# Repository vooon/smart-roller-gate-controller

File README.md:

# smart-roller-gate-controller
ESP32 based roller gate controller with ZigBee remotes

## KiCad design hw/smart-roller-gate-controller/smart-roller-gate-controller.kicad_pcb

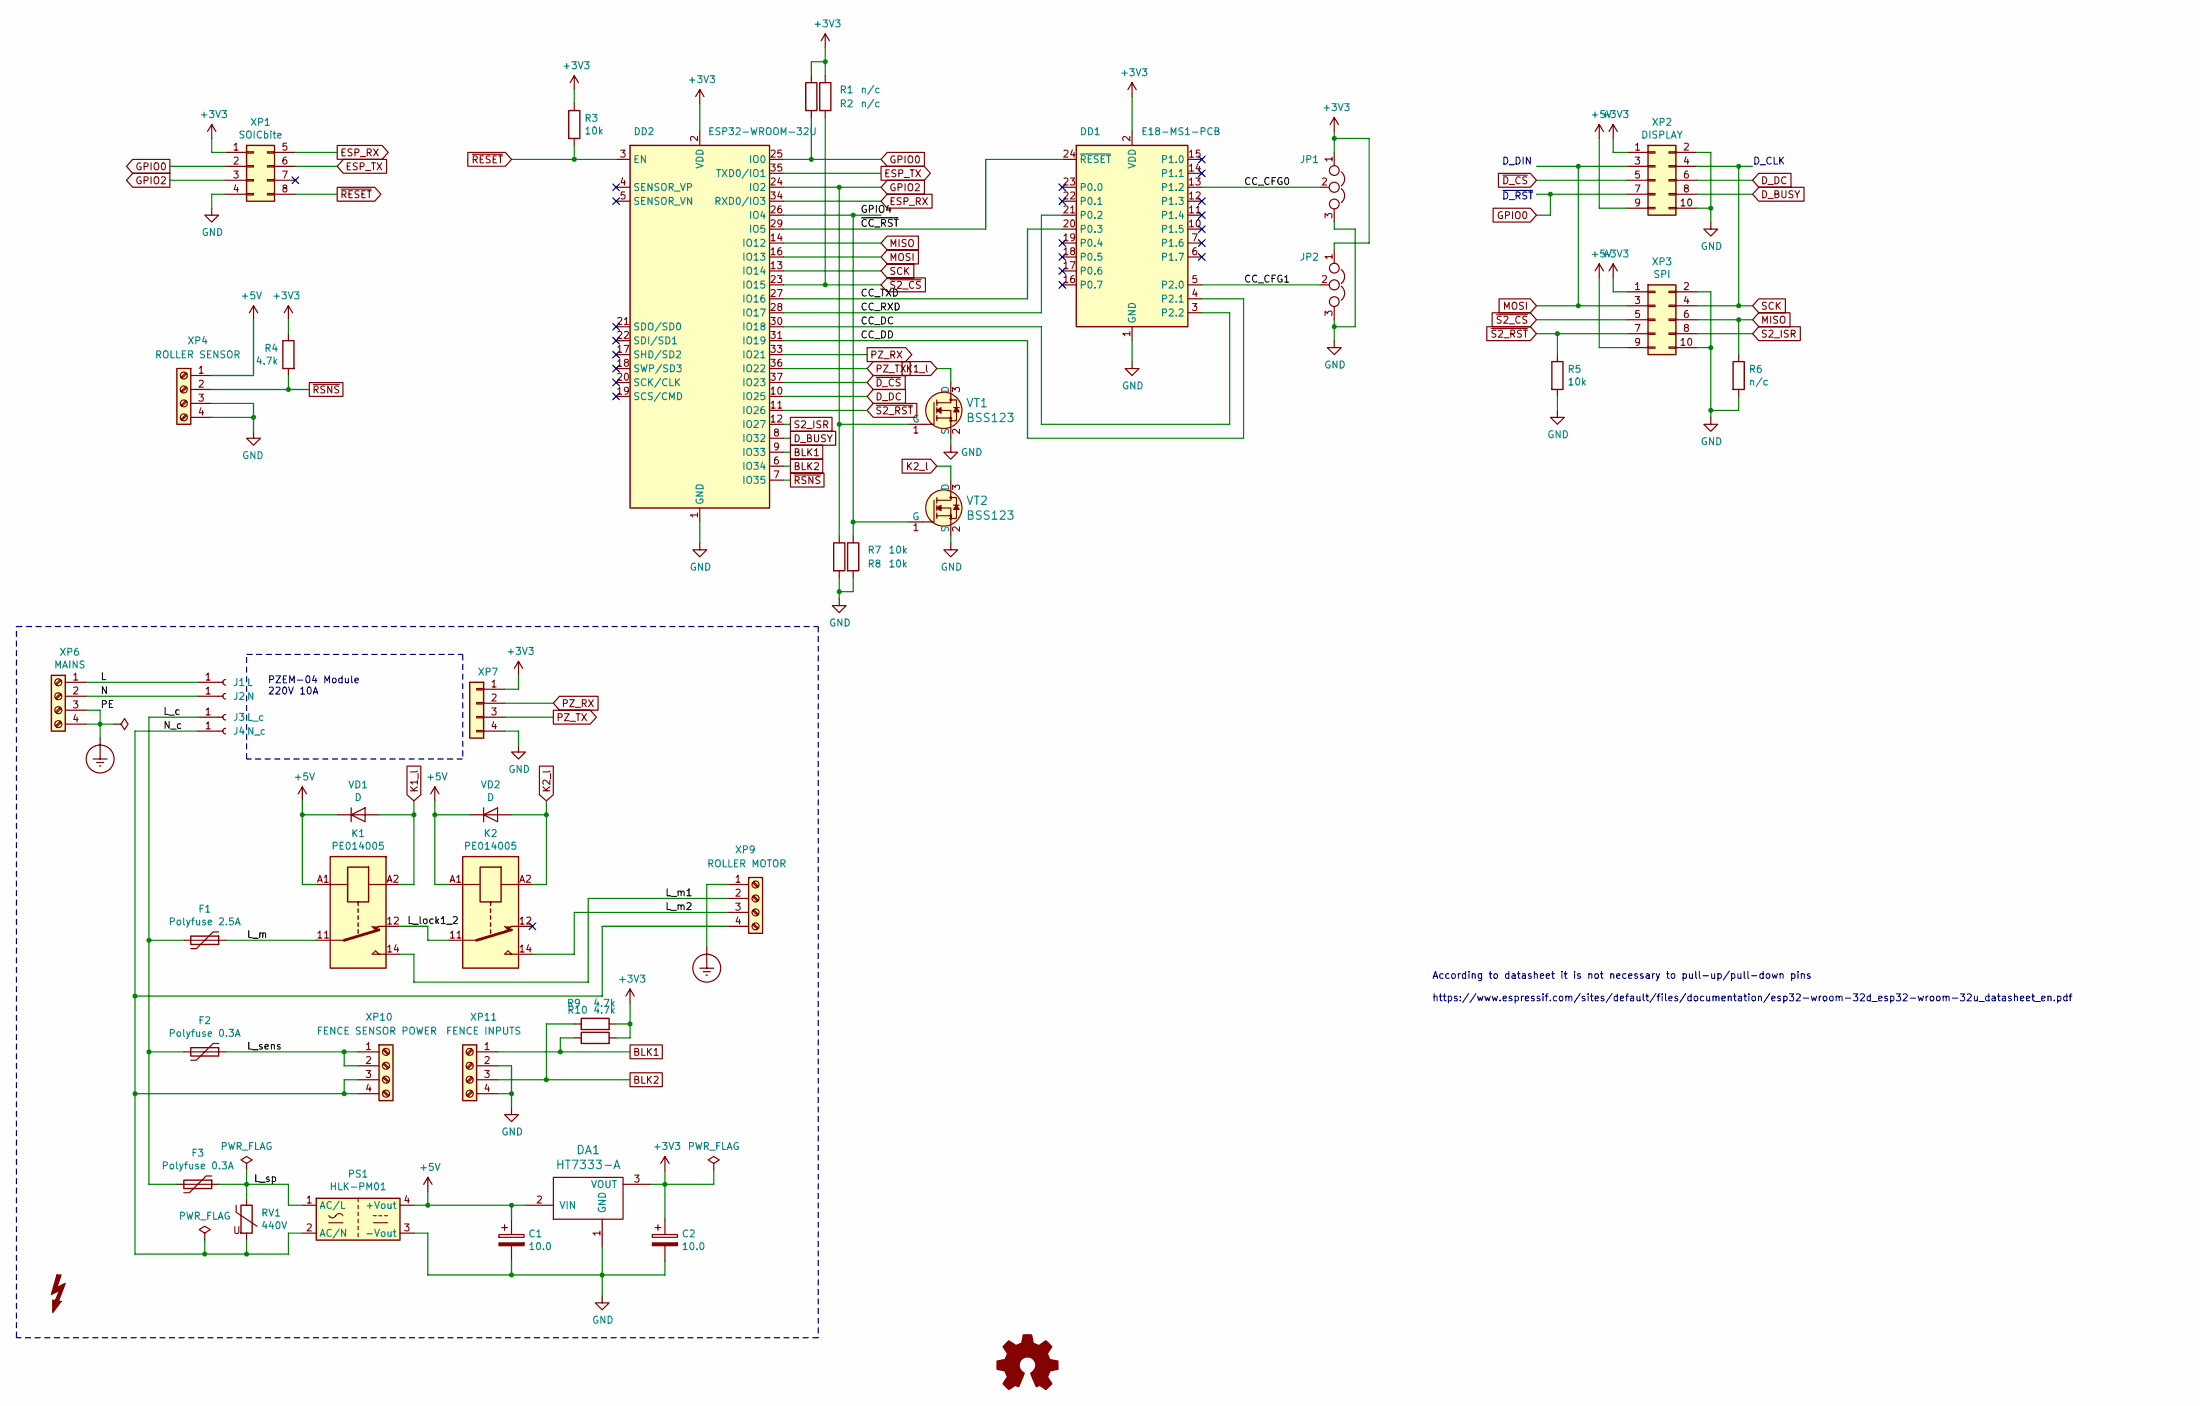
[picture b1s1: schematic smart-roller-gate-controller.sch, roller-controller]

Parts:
C1, C2: 10.0; CP_EIA-3216-10_Kemet-I
DA1: HT7333-A; SOT-89-3
DD1: E18-MS1-PCB
DD2: ESP32-WROOM-32U
F1: Polyfuse 2.5A; Fuse_Bourns_MF-RHT1300
F2, F3: Polyfuse 0.3A; Fuse_Bourns_MF-RHT200
J1: L; SolderWirePad_1x01_Drill1.2mm
J2: N; SolderWirePad_1x01_Drill1.2mm
J3: L_c; SolderWirePad_1x01_Drill1.2mm
J4: N_c; SolderWirePad_1x01_Drill1.2mm
JP1, JP2: Jumper_NC_Dual; SolderJumper-3_P1.3mm_Open_RoundedPad1.0x1.5mm
K1, K2: PE014005
PS1: HLK-PM01; Converter_ACDC_HiLink_HLK-PMxx
R1, R2, R6: n/c; R_0603_1608Metric_Pad1.05x0.95mm_HandSolder
R3, R5, R7, R8: 10k; R_0603_1608Metric_Pad1.05x0.95mm_HandSolder
R4, R9, R10: 4.7k; R_0603_1608Metric_Pad1.05x0.95mm_HandSolder
RV1: 440V; RV_Disc_D21.5mm_W4.9mm_P10mm
VD1, VD2: D; D_SOD-123
VT1, VT2: BSS123; SOT-23-3; MPN BSS123; Digi-Key_PN BSS123NCT-ND
XP1: SOICbite; SOIC_clipProgSmall
XP2: DISPLAY; CONN-TE-MICROMATCH-5X2-PTH-BOSS
XP3: SPI; CONN-TE-MICROMATCH-5X2-PTH-BOSS
XP4: ROLLER SENSOR; CONN-KF250-BA-4
XP6: MAINS; CONN-KF250-BA-4
XP7: Conn_01x04; JST_XH_B4B-XH-A_1x04_P2.50mm_Vertical
XP9: ROLLER MOTOR; CONN-KF250-BA-4
XP10: FENCE SENSOR POWER; CONN-KF250-BA-4
XP11: FENCE INPUTS; CONN-KF250-BA-4

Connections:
+3V3: C2.1, DA1.3 (VOUT), DD1.2 (VDD), DD2.2 (VDD), JP1.1, JP2.1, R1.1, R2.1, R3.1, R4.1, R9.2, R10.2, XP1.1, XP2.1, XP3.1, XP7.1
+5V: C1.1, DA1.2 (VIN), K1.A1, K2.A1, PS1.4 (+Vout), VD1.1 (K), VD2.1 (K), XP2.9, XP3.9, XP4.1
/CC_CFG0: DD1.13 (P1.2), JP1.2
/CC_CFG1: DD1.5 (P2.0), JP2.2
/CC_DC: DD1.3 (P2.2), DD2.30 (IO18)
/CC_DD: DD1.4 (P2.1), DD2.31 (IO19)
/CC_RXD: DD1.21 (P0.2), DD2.28 (IO17)
/CC_TXD: DD1.20 (P0.3), DD2.27 (IO16)
/GPIO4: DD2.26 (IO4), R8.1, VT2.1 (G)
/L: J1.1, XP6.1
/L_c: F1.2, F2.2, F3.2, J3.1
/L_lock1_2: K1.12, K2.11
/L_m: F1.1, K1.11
/L_m1: K1.14, XP9.2
/L_m2: K2.14, XP9.3
/L_sens: F2.1, XP10.1, XP10.2
/L_sp: F3.1, PS1.1 (AC/L), RV1.1
/N: J2.1, XP6.2
/N_c: J4.1, PS1.2 (AC/N), RV1.2, XP9.4, XP10.3, XP10.4
/~CC_RST: DD1.24 (~RESET), DD2.29 (IO5)
BLK1: DD2.9 (IO33), R10.1, XP11.1
BLK2: DD2.6 (IO34), R9.1, XP11.3
D_BUSY: DD2.8 (IO32), XP2.8
D_DC: DD2.10 (IO25), XP2.6
ESP_RX: DD2.34 (RXD0/IO3), XP1.5
ESP_TX: DD2.35 (TXD0/IO1), XP1.6
Earth_Protective: XP6.3, XP6.4, XP9.1
GND: C1.2, C2.2, DA1.1 (GND), DD1.1 (GND), DD2.1 (GND), DD2.15 (GND), DD2.38 (GND), JP1.3, JP2.3, PS1.3 (-Vout), R5.2, R6.2, R7.2, R8.2, VT1.2 (S), VT2.2 (S), XP1.4, XP2.2, XP2.10, XP3.2, XP3.10, XP4.3, XP4.4, XP7.4, XP11.2, XP11.4
GPIO0: DD2.25 (IO0), R1.2, XP1.2, XP2.7
GPIO2: DD2.24 (IO2), R7.1, VT1.1 (G), XP1.3
K1_l: K1.A2, VD1.2 (A), VT1.3 (D)
K2_l: K2.A2, VD2.2 (A), VT2.3 (D)
MISO: DD2.14 (IO12), R6.1, XP3.6
MOSI: DD2.16 (IO13), XP2.3, XP3.3
PZ_RX: DD2.33 (IO21), XP7.2
PZ_TX: DD2.36 (IO22), XP7.3
S2_ISR: DD2.12 (IO27), XP3.8
SCK: DD2.13 (IO14), XP2.4, XP3.4
~D_CS: DD2.37 (IO23), XP2.5
~RESET: DD2.3 (EN), R3.2, XP1.8
~RSNS: DD2.7 (IO35), R4.2, XP4.2
~S2_CS: DD2.23 (IO15), R2.2, XP3.5
~S2_RST: DD2.11 (IO26), R5.1, XP3.7

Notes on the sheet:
PZEM-04 Module 220V 10A
According to datasheet it is not necessary to pull-up/pull-down pins https://www.espressif.com/sites/default/files/documentation/esp32-wroom-32d_esp32-wroom-32u_datasheet_en.pdf
D_DIN
~D_RST
D_CLK

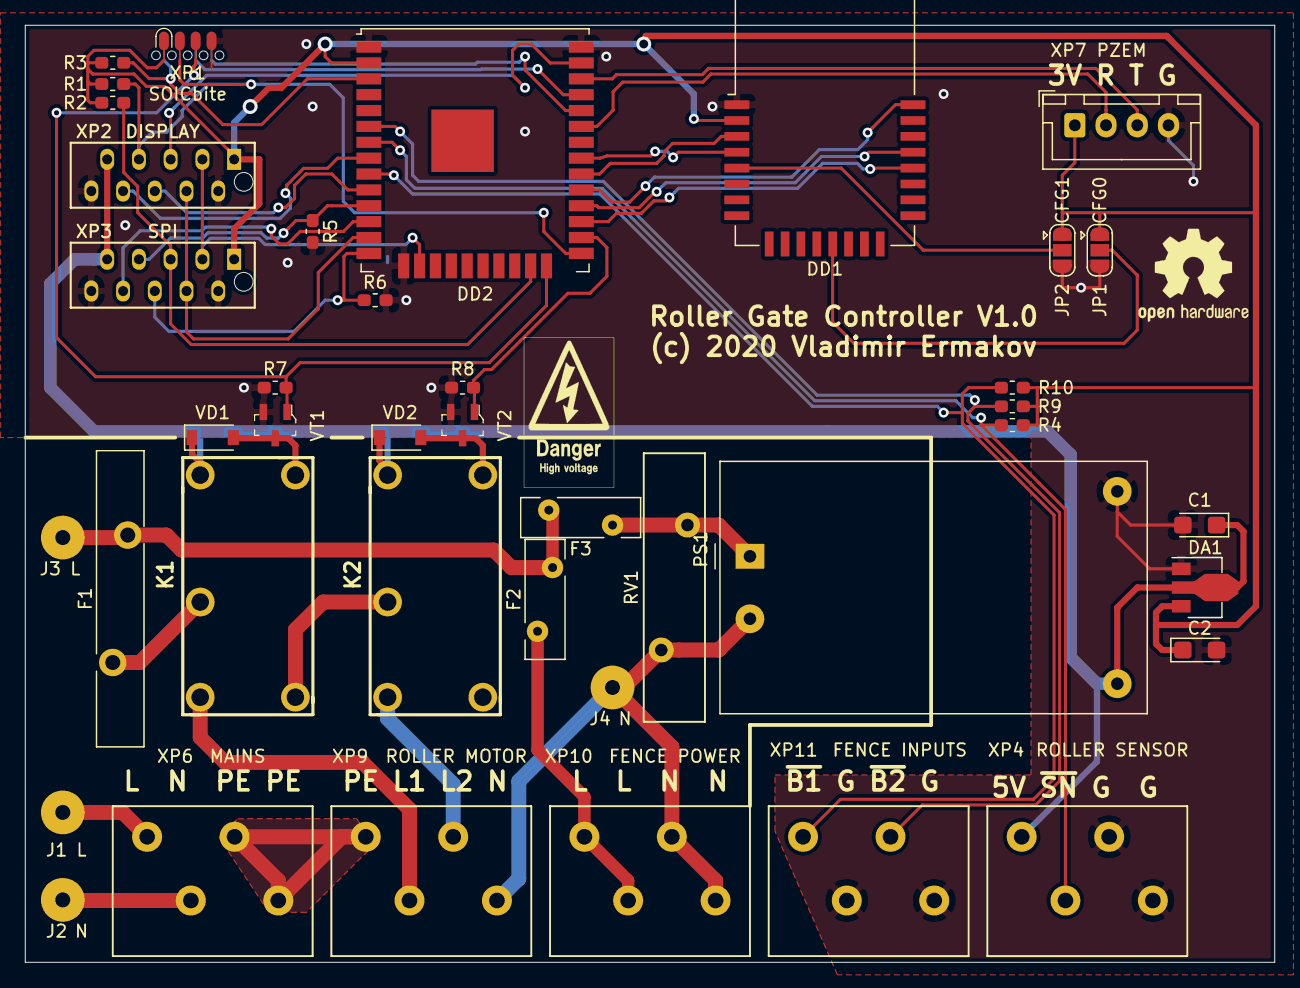
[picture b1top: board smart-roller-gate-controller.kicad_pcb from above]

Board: 2 copper layers, 100.0 x 75.0 mm, 41 parts (0 on the bottom side), 43 nets.

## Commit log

2020-01-19 hw: connect esp32 and cc2530
2020-01-19 hw: HLK-PM01 and HT7333 psu
2020-01-19 hw: mostly done hv sch
2020-01-20 hw: add debug connector
2020-01-20 hw: connect more patrs
2020-01-20 hw: sch complete, alpha version
2020-01-20 hw: optimize pinout a bit
2020-01-20 hw: start routing
2020-01-20 hw: initial placement
2020-01-25 hw: done initial placement
2020-01-26 hw: initial traces
2020-01-26 hw: done v1.0
2020-01-26 hw: add pcb production file for v1.0
2020-03-15 sw: add ESPHome initial configuration
2020-03-15 sw: use secrets file
2020-03-15 sw: define cover
2020-04-11 sw: add names for motor switches
2020-04-11 sw: use blk2 for Open/Close/Stop
2020-04-11 sw: disable display
2020-04-11 sw: implement all logic for blk1, blk2, rsns
2020-04-11 sw: make a common scripts for open/close/stop single and two buttons
2020-04-11 sw: make repeated press for Open/Close buttons possible. To Stop need to press opposete button
2020-04-11 sw: add device_class for blk1
2020-05-17 update config to use wifi_networks secret, add secters sample file
2020-06-07 esphome: delete display, won't be used here
2020-06-07 esphome: use pzem header to pair with old cover remote controller
2020-06-07 esphome: add cc reset on boot
2020-06-07 finally remove pzem, buggy sensor and unneded
2020-06-07 add switch to temporary disable blk1 (in some weather conditions sensor behaves badly)
2020-06-07 add ability to disable physical open/close button
2020-06-07 add reset_counters service
2020-06-07 fix id/name
2020-06-07 rename yml -> yaml
2020-06-08 add units to counters (to see them on graphs)
2020-06-10 esphome: reduce open/close durations to 30s (measured about 20s)
2020-09-13 esphome: update prometheus integration for esphome 1.15
2020-11-20 esphome: use substitution
2020-12-06 esphome: add hack to always fully close the door when RSNS activates
2021-10-26 sync with HA
2021-10-26 update to ESP IDF
2021-10-26 add zigbee router pairing service
2021-10-26 add second door config

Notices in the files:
hw/smart-roller-gate-controller/smart-roller-gate-controller.kicad_pcb:
(c) 2020 Vladimir Ermakov
